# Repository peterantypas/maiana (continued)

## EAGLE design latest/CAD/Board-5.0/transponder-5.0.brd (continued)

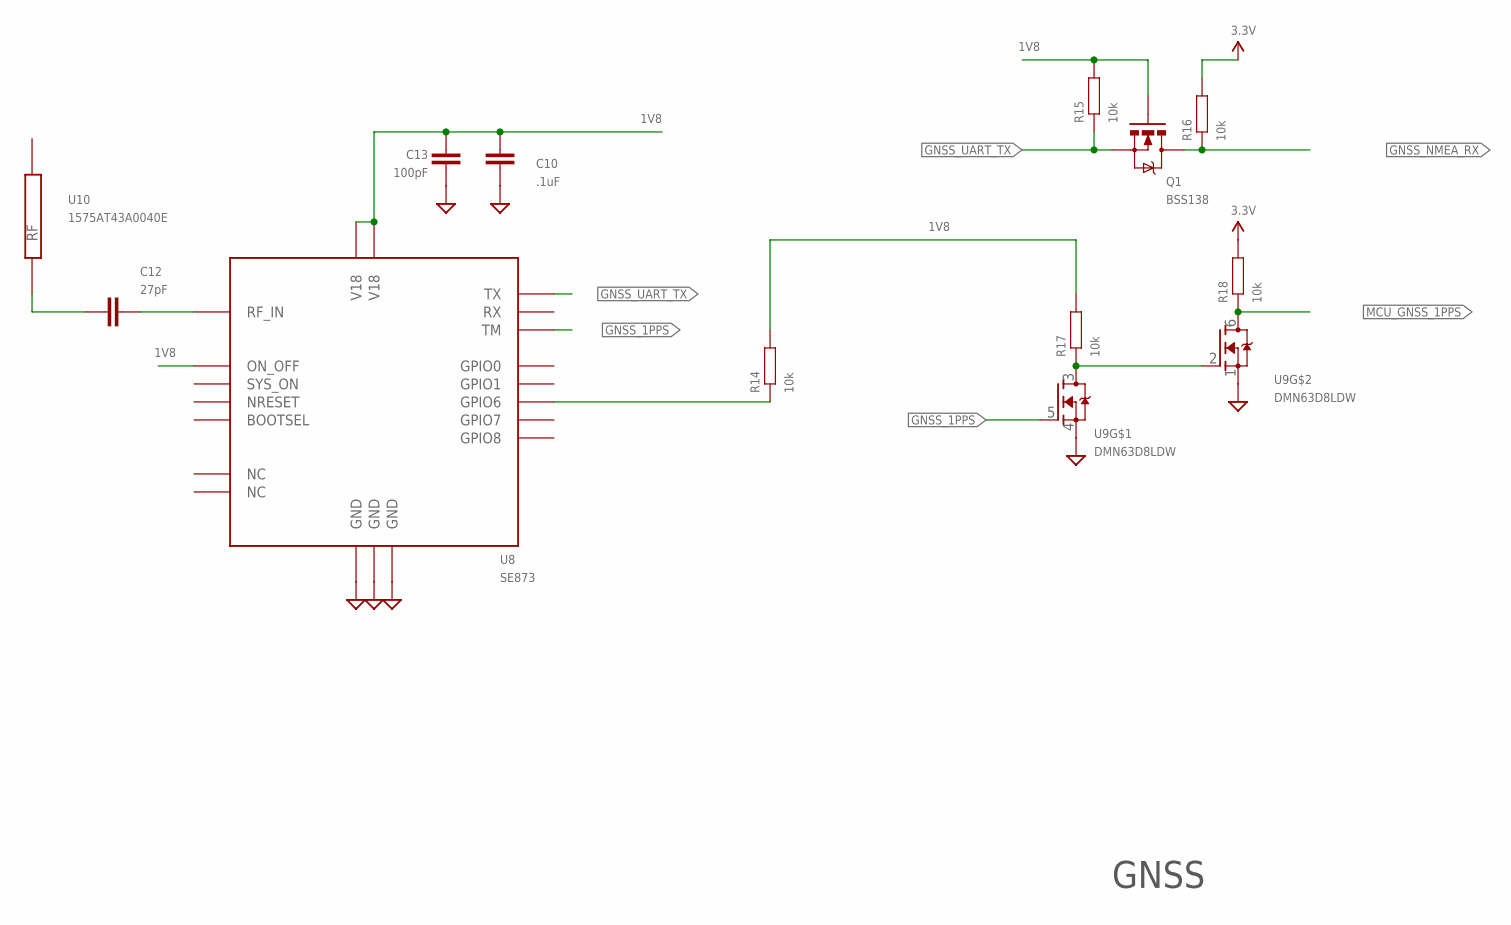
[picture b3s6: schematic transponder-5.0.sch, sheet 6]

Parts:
C10: .1uF; 0603-CAP
C12: 27pF; 0603-CAP
C13: 100pF; 0603-CAP
Q1: BSS138; SOT23-3
R14, R15, R16, R17, R18: 10k; 0603-RES
U8: SE873
U9: DMN63D8LDW; SOT363
U10: 1575AT43A0040E

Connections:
1V8: C10.1, C13.1, Q1.1 (G), R14.2, R15.2, R17.2, U8.P$3 (V18), U8.P$6 (ON_OFF), U8.P$19 (V18); also elsewhere on the board
3.3V: R16.2, R18.2; also elsewhere on the board
GND: C10.2, C13.2, U8.P$2 (GND), U8.P$10 (GND), U8.P$20 (GND), U9.1 (S), U9.4 (S); also elsewhere on the board
GNSS_1PPS: U8.P$11 (TM), U9.5 (G)
GNSS_NMEA_RX: Q1.3 (D), R16.1; also elsewhere on the board
GNSS_UART_TX: Q1.2 (S), R15.1, U8.P$15 (TX)
MCU_GNSS_1PPS: R18.1, U9.6 (D); also elsewhere on the board
unnamed: C12.2, U8.P$1 (RF_IN)
unnamed: C12.1, U10.P$1 (RF)
unnamed: R17.1, U9.2 (G), U9.3 (D)
unnamed: R14.1, U8.P$13 (GPIO6)

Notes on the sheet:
GNSS

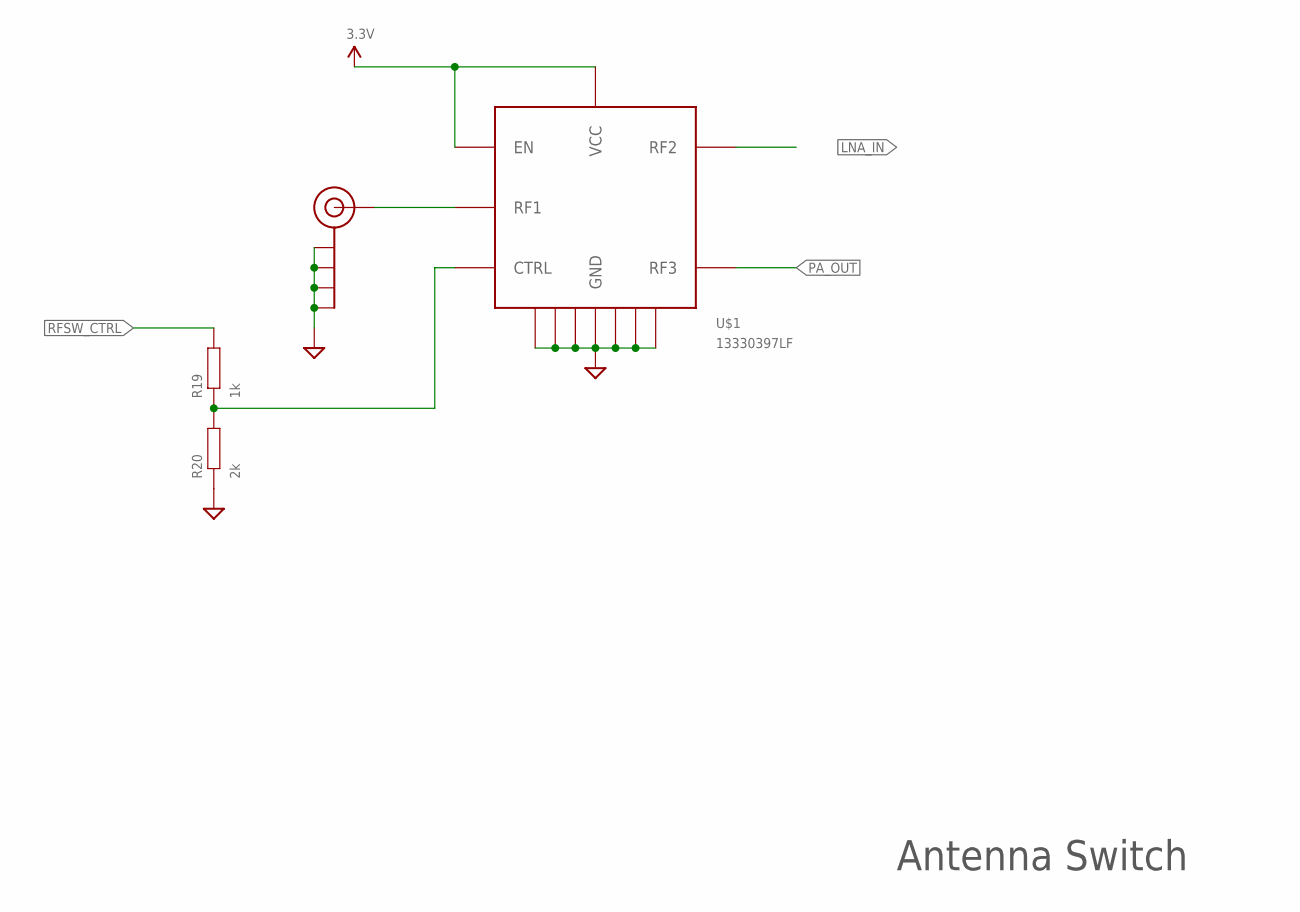
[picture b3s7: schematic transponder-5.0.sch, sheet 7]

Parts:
J$1: SMA_EDGE; SMA-EDGE
R19: 1k; 0603-RES
R20: 2k; 0603-RES
U$1: 13330397LF; QFN12

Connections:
3.3V: U$1.P$8 (EN), U$1.P$9 (VCC); also elsewhere on the board
GND: J$1.GND@0 (GND), J$1.GND@1 (GND), J$1.GND@2 (GND), J$1.GND@3 (GND), R20.1, U$1.P$1 (GND), U$1.P$3 (GND), U$1.P$4 (GND), U$1.P$6 (GND), U$1.P$10 (GND), U$1.P$12 (GND), U$1.P$13 (GND); also elsewhere on the board
LNA_IN: U$1.P$11 (RF2); also elsewhere on the board
unnamed: R19.1, R20.2, U$1.P$7 (CTRL)
unnamed: J$1.SIG (SIGNAL), U$1.P$2 (RF1)
PA_OUT: U$1.P$5 (RF3); also elsewhere on the board
RFSW_CTRL: R19.2; also elsewhere on the board

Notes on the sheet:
Antenna Switch

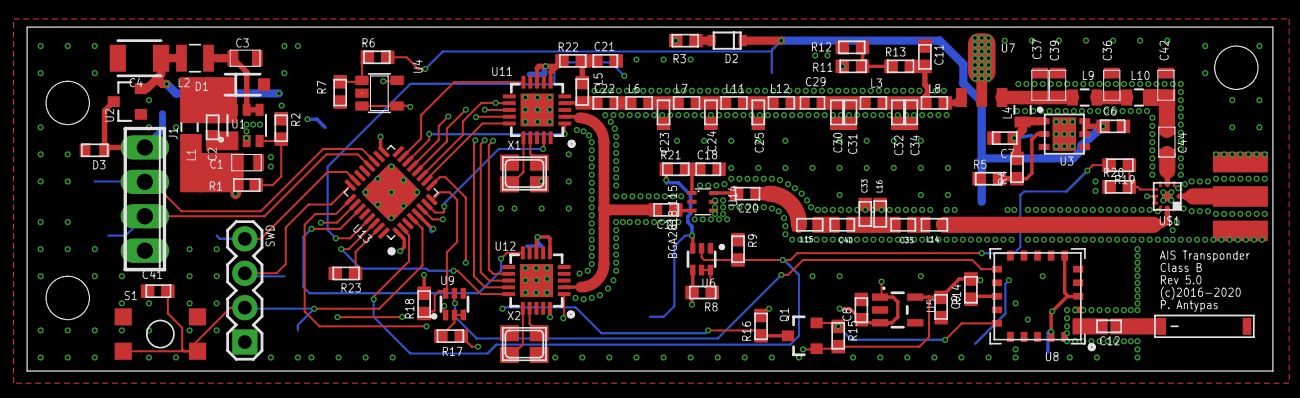
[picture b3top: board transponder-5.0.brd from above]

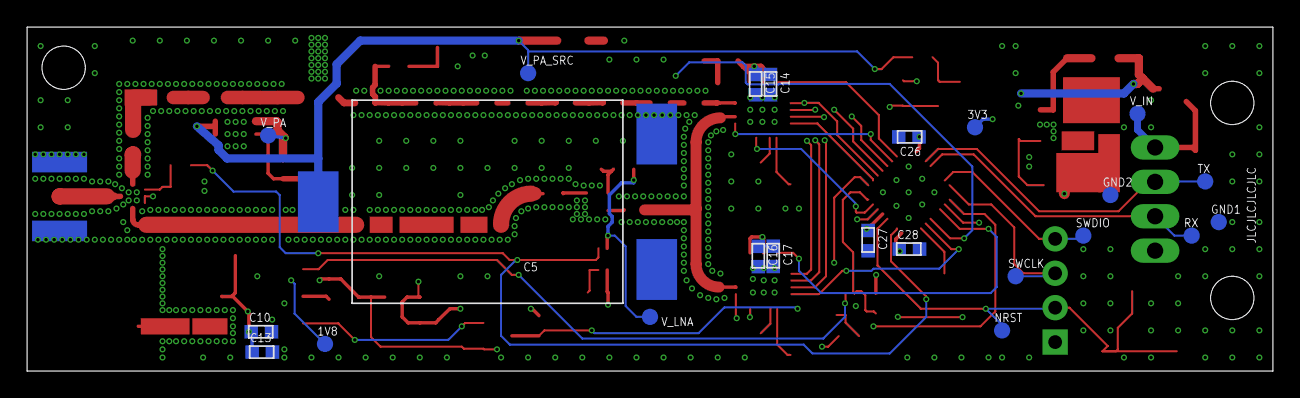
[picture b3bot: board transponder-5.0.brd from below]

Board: 4 copper layers, 92.0 x 25.4 mm, 117 parts (23 on the bottom side), 74 nets.

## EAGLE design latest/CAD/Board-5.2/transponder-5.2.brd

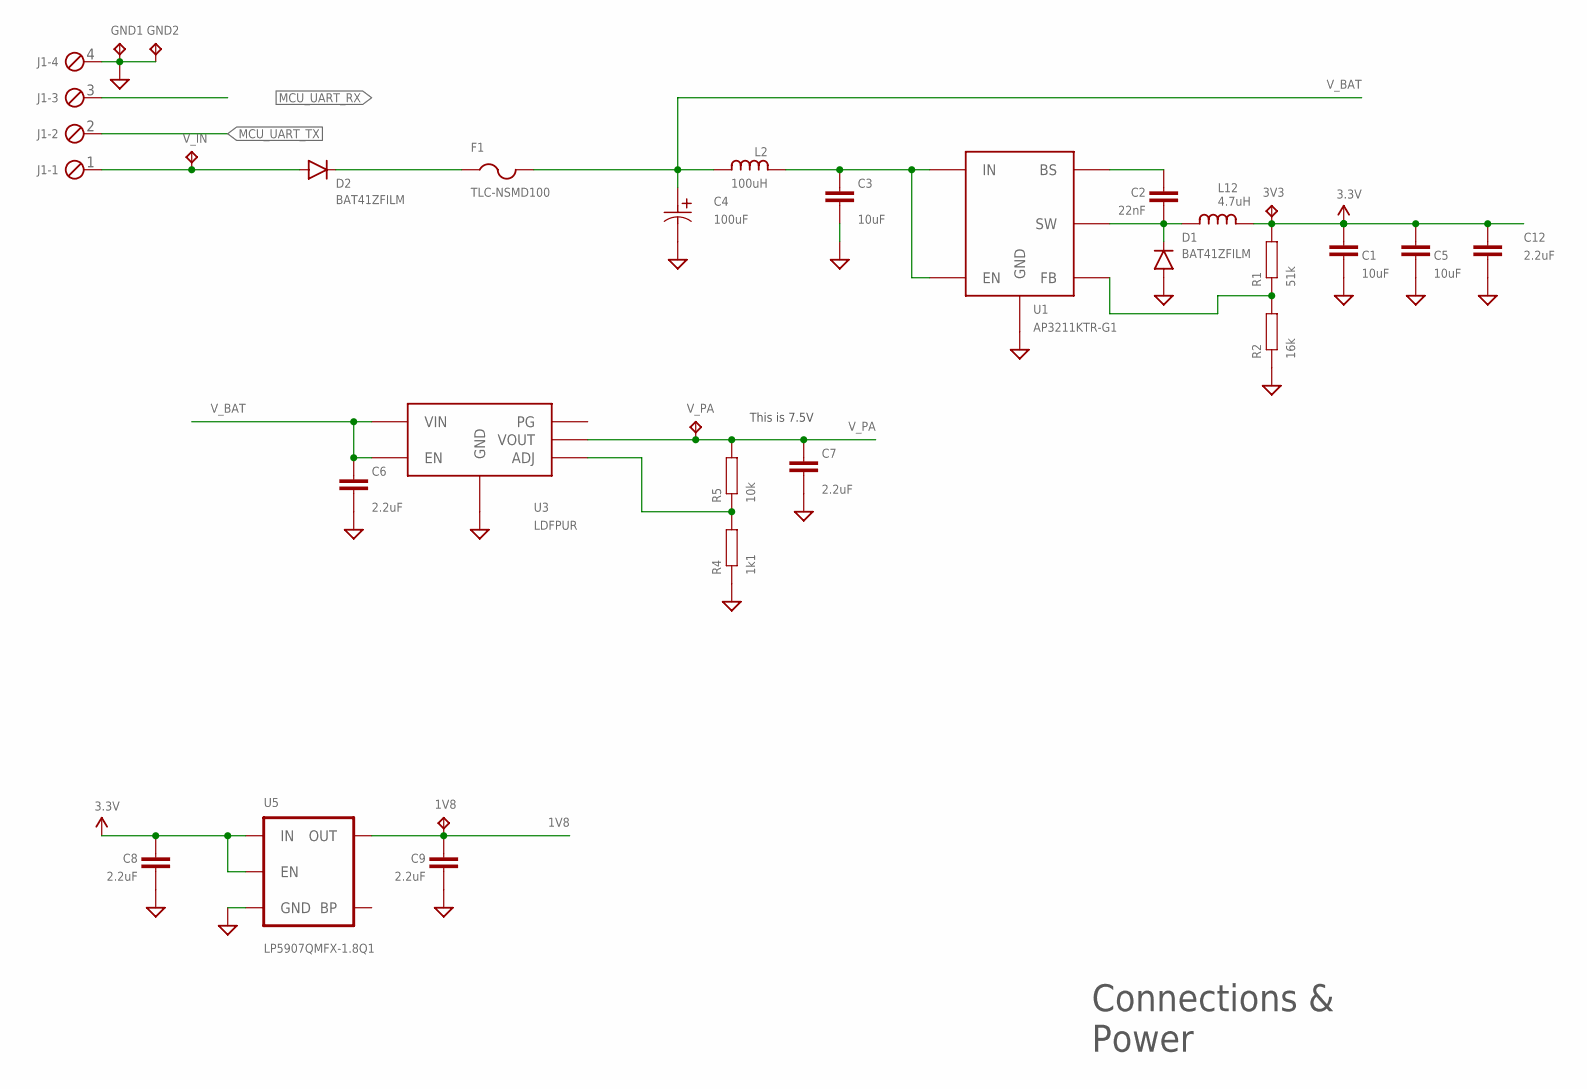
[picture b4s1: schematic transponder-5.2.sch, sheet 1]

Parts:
1V8, 3V3: TPTP16R; TP16R
C1, C3, C5: 10uF; 0805; PARTNO EMK212ABJ106KG-T
C2: 22nF; 0603-CAP; PARTNO GRM188R71E223KA01D
C4: 100uF; PCAP_6.3X5.4-ELECT; PARTNO UWX1C101MCL1GB
C6, C7, C8, C9, C12: 2.2uF; 0603-CAP; PARTNO EMK107BJ225KA-T
D1, D2: BAT41ZFILM; SOD-123; PARTNO BAT41ZFILM
F1: TLC-NSMD100; R1206; PARTNO TLC-NSMD100
GND1, GND2: TPTP16R; TP16R
J1: MPT4; 4POL254
L2: 100uH; 1206; PARTNO CBC3225T101KRV
L12: 4.7uH; 0805; PARTNO MLZ2012M4R7WT000
R1: 51k; 0603-RES; PARTNO RC0603JR-0751KL
R2: 16k; 0603-RES; PARTNO RC0603FR-1016KL
R4: 1k1; 0603-RES; PARTNO RC0603JR-071K1L
R5: 10k; 0603-RES; PARTNO RC0603JR-0710KL
U1: AP3211KTR-G1; SOT23-6; PARTNO AP3211KTR-G1
U3: LDFPUR; DFN-6; PARTNO LDFPUR
U5: LP5907QMFX-1.8Q1; SOT23-5; PARTNO LP5907QMFX-1.8Q1
V_IN: TPTP16R; TP16R
V_PA: TPTP16R; TP16R

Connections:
1V8: 1V8.TP, C9.1, U5.5 (OUT); also elsewhere on the board
3.3V: 3V3.TP, C1.1, C5.1, C8.1, C12.1, L12.P$2, R1.2, U5.1 (IN), U5.3 (EN); also elsewhere on the board
GND: C1.2, C3.2, C4.2 (22), C5.2, C6.2, C7.2, C8.2, C9.2, C12.2, D1.A, GND1.TP, GND2.TP, J1.4, R2.1, R4.1, U1.2 (GND), U3.P$4 (GND), U3.P$7 (GND), U5.2 (GND); also elsewhere on the board
MCU_UART_RX: J1.3; also elsewhere on the board
MCU_UART_TX: J1.2; also elsewhere on the board
unnamed: C3.1, L2.P$1, U1.4 (EN), U1.5 (IN)
unnamed: C2.2, D1.C, L12.P$1, U1.6 (SW)
unnamed: C2.1, U1.1 (BS)
unnamed: R1.1, R2.2, U1.3 (FB)
unnamed: R4.2, R5.1, U3.P$2 (ADJ)
unnamed: D2.C, F1.1
V_BAT: C4.1 (11), C6.1, F1.2, L2.P$2, U3.P$5 (EN), U3.P$6 (VIN)
V_IN: D2.A, J1.1, V_IN.TP
V_PA: C7.1, R5.2, U3.P$1 (VOUT), V_PA.TP; also elsewhere on the board

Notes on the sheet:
Connections & Power
This is 7.5V

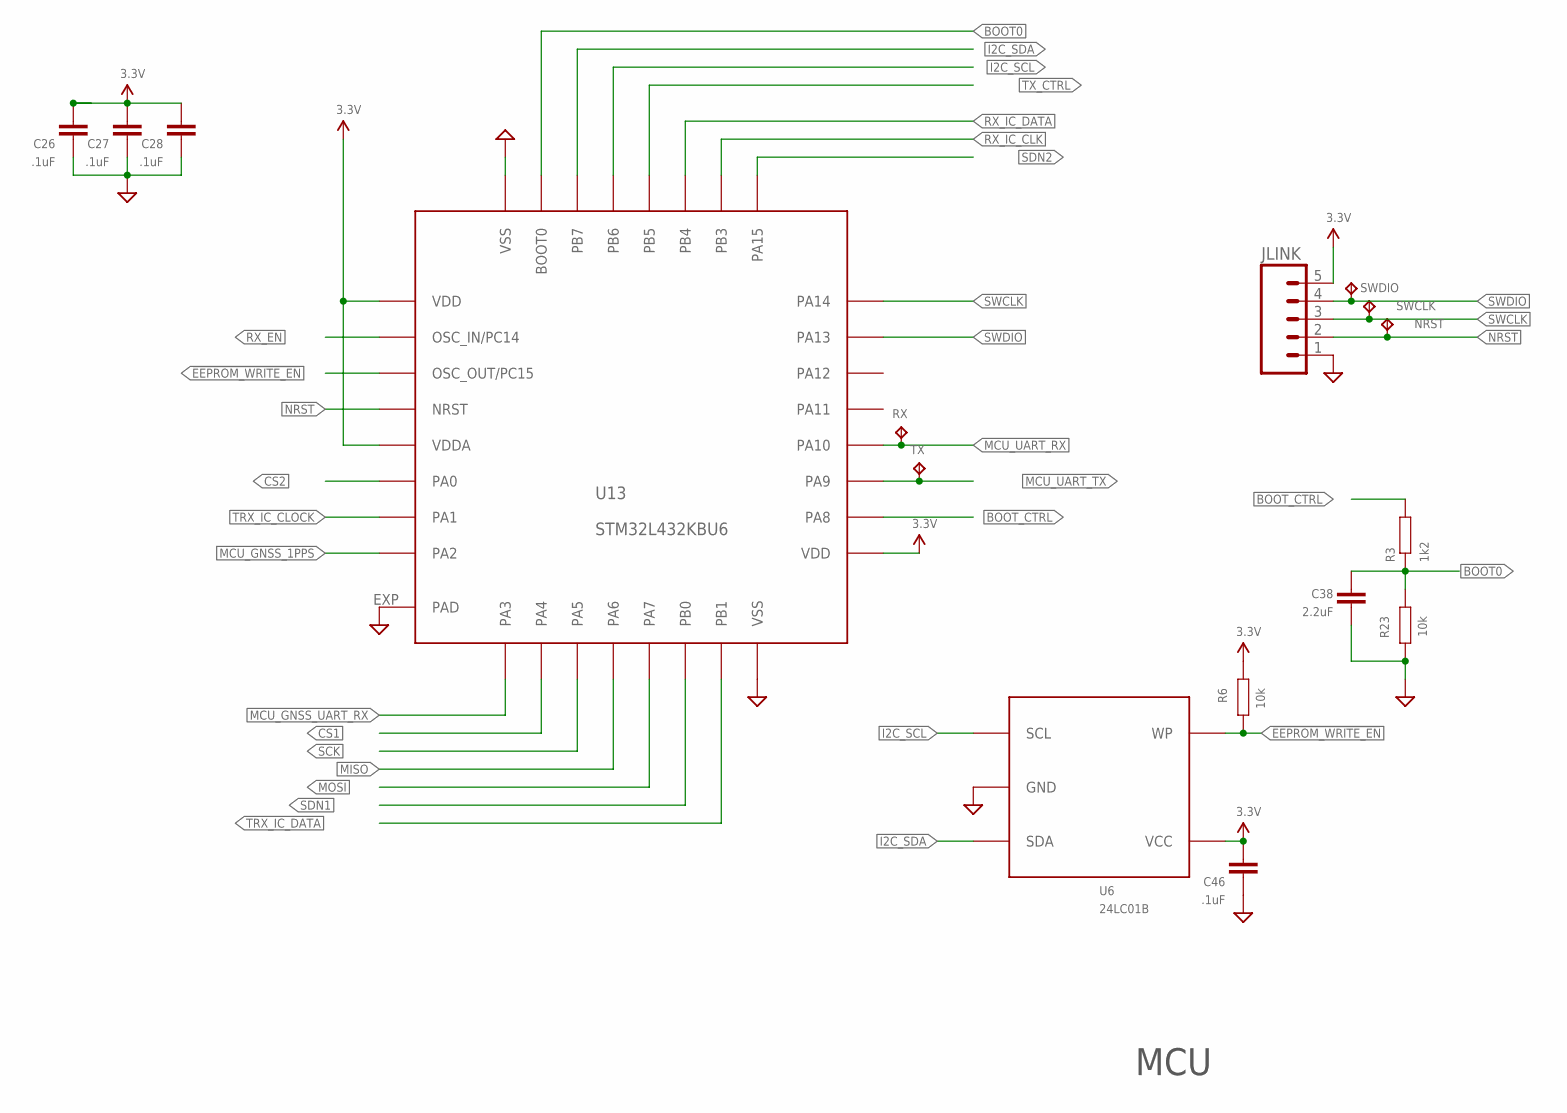
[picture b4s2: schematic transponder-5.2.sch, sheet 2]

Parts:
C26, C27, C28, C46: .1uF; 0603-CAP; PARTNO EMK107B7104KAHT
C38: 2.2uF; 0603-CAP; PARTNO EMK107BJ225KA-T
JLINK: M05PTH; 1X05
NRST: TPTP16R; TP16R
R3: 1k2; 0603-RES; PARTNO RC0603JR-071K2L
R6, R23: 10k; 0603-RES; PARTNO RC0603JR-0710KL
RX: TPTP16R; TP16R
SWCLK: TPTP16R; TP16R
SWDIO: TPTP16R; TP16R
TX: TPTP16R; TP16R
U6: 24LC01B; SOT23-5; PARTNO 24LC01BT-I/OT
U13: STM32L432KBU6; QFN32; PARTNO STM32L431KBU6

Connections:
3.3V: C26.1, C27.1, C28.1, C46.1, JLINK.5, R6.1, U6.4 (VCC), U13.1 (VDD), U13.5 (VDDA), U13.17 (VDD); also elsewhere on the board
!EEPROM_WRITE_EN: R6.2, U6.5 (WP), U13.3 (OSC_OUT/PC15)
BOOT0: C38.1, R3.1, R23.1, U13.31 (BOOT0)
BOOT_CTRL: R3.2, U13.18 (PA8)
CS1: U13.10 (PA4); also elsewhere on the board
CS2: U13.6 (PA0); also elsewhere on the board
GND: C26.2, C27.2, C28.2, C38.2, C46.2, JLINK.1, R23.2, U6.2 (GND), U13.16 (VSS), U13.32 (VSS), U13.EXP (PAD); also elsewhere on the board
I2C_SCL: U6.1 (SCL), U13.29 (PB6)
I2C_SDA: U6.3 (SDA), U13.30 (PB7)
MCU_GNSS_1PPS: U13.8 (PA2); also elsewhere on the board
MCU_GNSS_UART_RX: U13.9 (PA3); also elsewhere on the board
MCU_UART_RX: RX.TP, U13.20 (PA10); also elsewhere on the board
MCU_UART_TX: TX.TP, U13.19 (PA9); also elsewhere on the board
MISO: U13.12 (PA6); also elsewhere on the board
MOSI: U13.13 (PA7); also elsewhere on the board
NRST: JLINK.2, NRST.TP, U13.4 (NRST)
RX_EN: U13.2 (OSC_IN/PC14); also elsewhere on the board
RX_IC_CLK: U13.26 (PB3); also elsewhere on the board
RX_IC_DATA: U13.27 (PB4); also elsewhere on the board
SCK: U13.11 (PA5); also elsewhere on the board
SDN1: U13.14 (PB0); also elsewhere on the board
SDN2: U13.25 (PA15); also elsewhere on the board
SWCLK: JLINK.3, SWCLK.TP, U13.24 (PA14)
SWDIO: JLINK.4, SWDIO.TP, U13.23 (PA13)
TRX_IC_CLOCK: U13.7 (PA1); also elsewhere on the board
TRX_IC_DATA: U13.15 (PB1); also elsewhere on the board
TX_CTRL: U13.28 (PB5); also elsewhere on the board

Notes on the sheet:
MCU

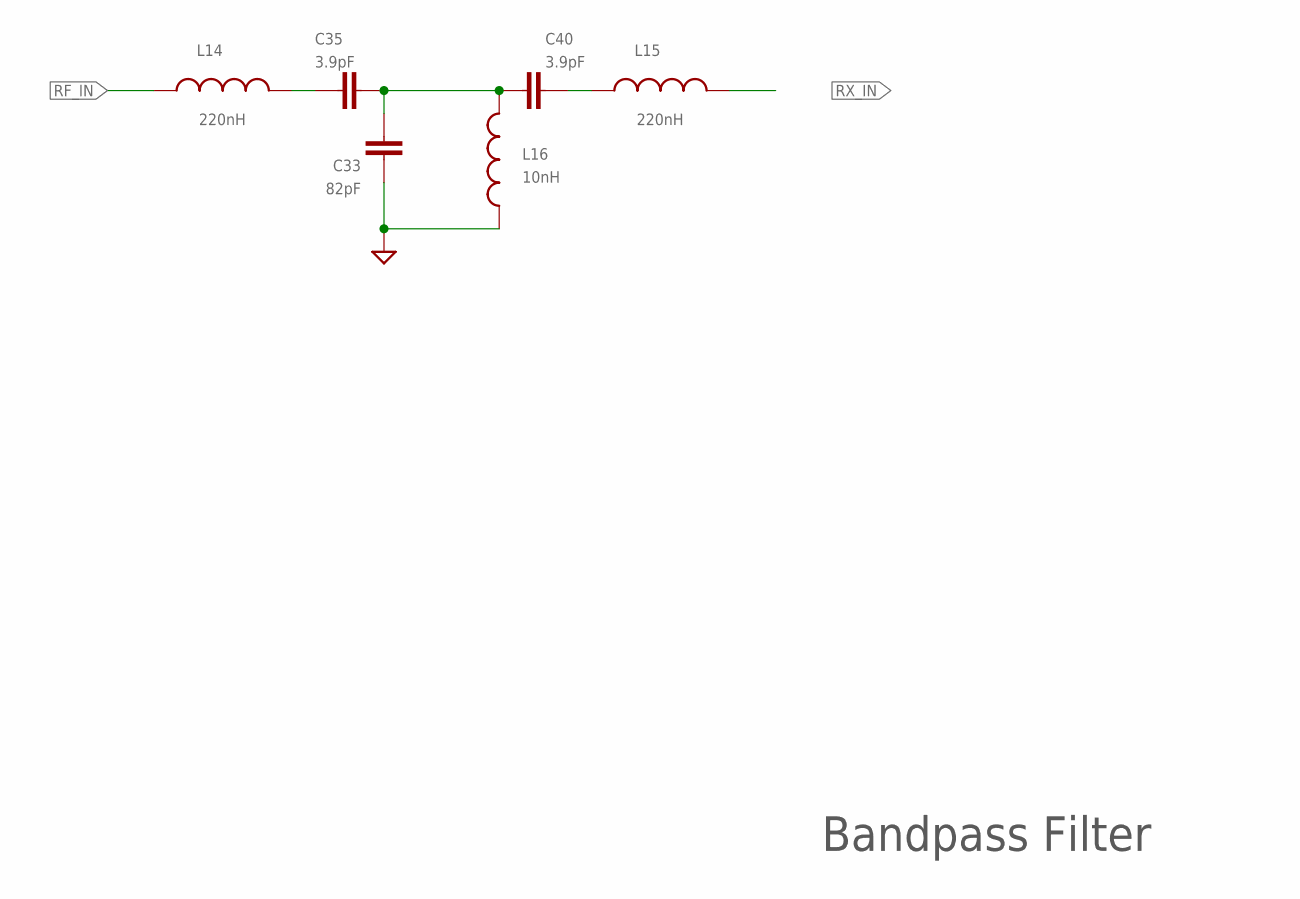
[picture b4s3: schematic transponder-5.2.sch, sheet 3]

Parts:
C33: 82pF; 0603-CAP
C35, C40: 3.9pF; 0603-CAP; PARTNO GCM1885C2A3R9BA16D
L14, L15: 220nH; 0603
L16: 10nH; 0603; PARTNO LQW18AS10NJ0CD

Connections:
GND: C33.1, L16.1; also elsewhere on the board
unnamed: C33.2, C35.1, C40.2, L16.2
unnamed: C40.1, L15.1
unnamed: C35.2, L14.2
RF_IN: L14.1; also elsewhere on the board
RX_IN: L15.2; also elsewhere on the board

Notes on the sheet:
Bandpass Filter

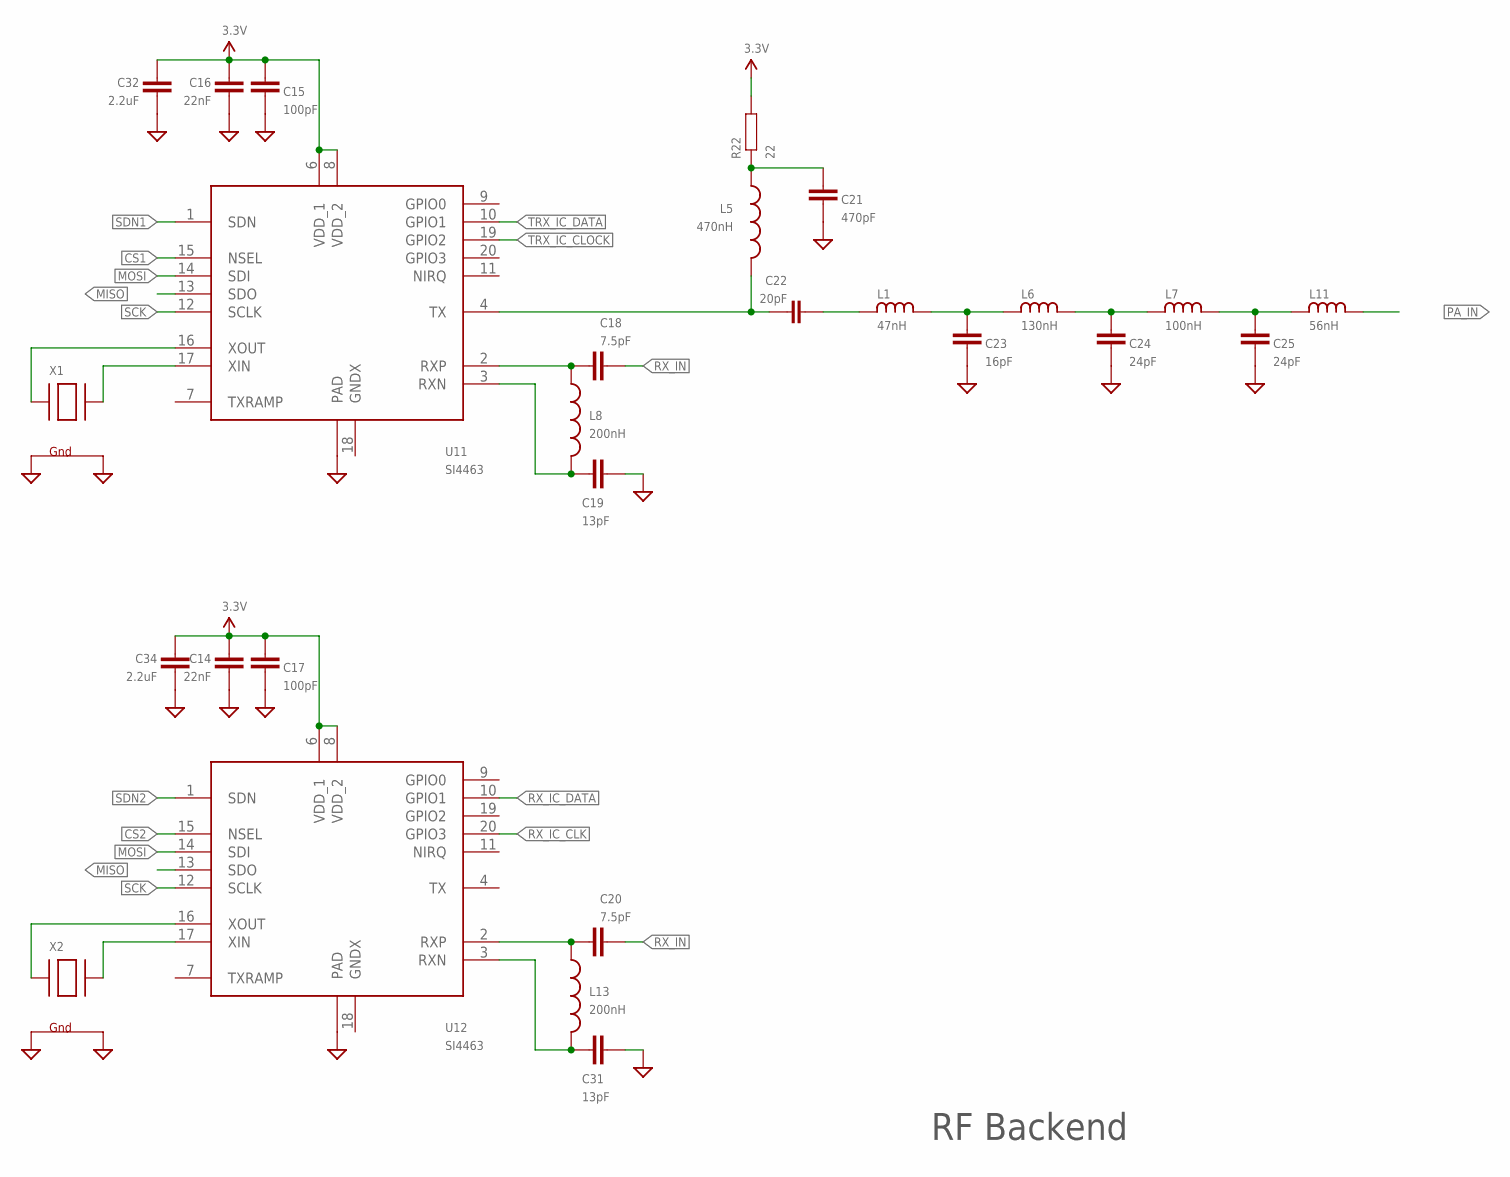
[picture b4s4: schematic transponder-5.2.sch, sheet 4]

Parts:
C14, C16: 22nF; 0603-CAP; PARTNO GRM188R71E223KA01D
C15, C17: 100pF; 0603-CAP; PARTNO GCM1885C2A101JA16D
C18, C20: 7.5pF; 0603-CAP; PARTNO GRM1885C1H7R5DA01D
C19, C31: 13pF; 0603-CAP; PARTNO GRM1885C1H130JA01D
C21: 470pF; 0603-CAP; PARTNO GCM1885C2A471JA16J
C22: 20pF; 0603; PARTNO GRM1885C1H200JA01D
C23: 16pF; 0603-CAP; PARTNO GCM1885C2A160JA16D
C24, C25: 24pF; 0603-CAP; PARTNO GCM1885C2A240JA16D
C32, C34: 2.2uF; 0603-CAP; PARTNO EMK107BJ225KA-T
L1: 47nH; 0603; PARTNO LQW18AS47NG00D
L5: 470nH; 0603; PARTNO HK1608R47J-T
L6: 130nH; 0603; PARTNO LQW18ANR13G00D
L7: 100nH; 0603; PARTNO LQW18ANR10G00D
L8, L13: 200nH; 0603; PARTNO LQW18ANR20J00D
L11: 56nH; 0603; PARTNO LQW18AN56NG00D
R22: 22; 0603-RES; PARTNO RC0603JR-0722RL
U11, U12: SI4463; PARTNO SI4463-C2A-GMR
X1, X2: XTAL-4-3225; NX3225; PARTNO CX3225SB30000D0FPLCC

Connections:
3.3V: C14.1, C15.1, C16.1, C17.1, C32.1, C34.1, R22.2, U11.6 (VDD_1), U11.8 (VDD_2), U12.6 (VDD_1), U12.8 (VDD_2); also elsewhere on the board
CS1: U11.15 (NSEL); also elsewhere on the board
CS2: U12.15 (NSEL); also elsewhere on the board
GND: C14.2, C15.2, C16.2, C17.2, C19.1, C21.2, C23.2, C24.2, C25.2, C31.1, C32.2, C34.2, U11.EXP (PAD), U12.EXP (PAD), X1.2 (G2), X1.4 (G1), X2.2 (G2), X2.4 (G1); also elsewhere on the board
MISO: U11.13 (SDO), U12.13 (SDO); also elsewhere on the board
MOSI: U11.14 (SDI), U12.14 (SDI); also elsewhere on the board
unnamed: C19.2, L8.2, U11.3 (RXN)
unnamed: C18.1, L8.1, U11.2 (RXP)
unnamed: C24.1, L6.P$2, L7.P$1
unnamed: C25.1, L7.P$2, L11.P$1
unnamed: C23.1, L1.P$2, L6.P$1
unnamed: U12.16 (XOUT), X2.1 (X1)
unnamed: U12.17 (XIN), X2.3 (X2)
unnamed: U11.16 (XOUT), X1.1 (X1)
unnamed: U11.17 (XIN), X1.3 (X2)
unnamed: C20.1, L13.1, U12.2 (RXP)
unnamed: C31.2, L13.2, U12.3 (RXN)
unnamed: C22.P$1, L5.2, U11.4 (TX)
unnamed: C21.1, L5.1, R22.1
unnamed: C22.P$2, L1.P$1
PA_IN: L11.P$2; also elsewhere on the board
RX_IC_CLK: U12.20 (GPIO3); also elsewhere on the board
RX_IC_DATA: U12.10 (GPIO1); also elsewhere on the board
RX_IN: C18.2, C20.2; also elsewhere on the board
SCK: U11.12 (SCLK), U12.12 (SCLK); also elsewhere on the board
SDN1: U11.1 (SDN); also elsewhere on the board
SDN2: U12.1 (SDN); also elsewhere on the board
TRX_IC_CLOCK: U11.19 (GPIO2); also elsewhere on the board
TRX_IC_DATA: U11.10 (GPIO1); also elsewhere on the board

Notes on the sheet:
RF Backend

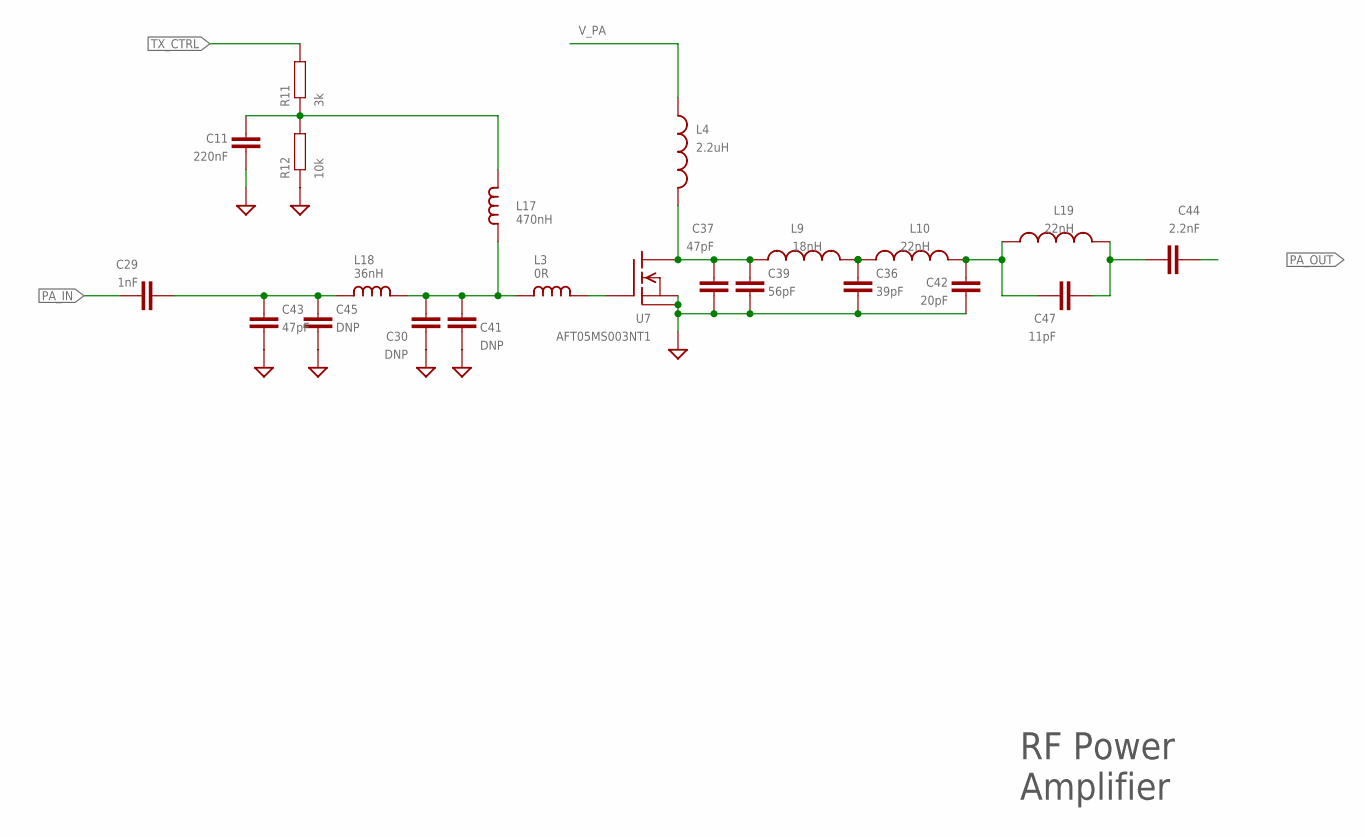
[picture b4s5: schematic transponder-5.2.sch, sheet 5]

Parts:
C11: 220nF; 0603-CAP
C29: 1nF; 0603-CAP; PARTNO GRM1885C1H102JA01D
C30: DNP; 0603-CAP; PARTNO GCM1885C2A101JA16D
C36: 39pF; 0603-CAP; PARTNO GRM1885C1H390JA01D
C37, C43: 47pF; 0603-CAP
C39: 56pF; 0603-CAP; PARTNO GRM1885C1H560JA01D
C41: DNP; 0603-CAP; PARTNO Murata Electronics
C42: 20pF; 0603-CAP; PARTNO GRM1885C1H200JA01D
C44: 2.2nF; 0603-CAP; PARTNO GRM1885C1H222JA01J
C45: DNP; 0603-CAP; PARTNO GRM1885C1H560JA01D
C47: 11pF; 0603-CAP; PARTNO GRM1885C1H110JA01D
L3: 0R; 0603; PARTNO LQW18AN11NJ00D
L4: 2.2uH; 0805; PARTNO BRC2012T2R2MD
L9: 18nH; 0603; PARTNO LQW18AN18NG00D
L10, L19: 22nH; 0603; PARTNO LQW18AN22NJ00D
L17: 470nH; 0603; PARTNO HK1608R47J-T
L18: 36nH; 0603
R11: 3k; 0603-RES
R12: 10k; 0603-RES; PARTNO RC0603JR-0710KL
U7: AFT05MS003NT1; SOT-89; PARTNO AFT05MS003NT1

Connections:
GND: C11.2, C30.2, C36.2, C37.2, C39.2, C41.2, C42.2, C43.2, C45.2, R12.1, U7.2 (S), U7.2@1 (PAD); also elsewhere on the board
unnamed: C11.1, L17.P$2, R11.1, R12.2
unnamed: C37.1, C39.1, L4.2, L9.1, U7.3 (D)
unnamed: L3.P$2, U7.1 (G)
unnamed: C36.1, L9.2, L10.1
unnamed: C29.2, C43.1, C45.1, L18.P$1
unnamed: C30.1, C41.1, L3.P$1, L17.P$1, L18.P$2
unnamed: C44.1, C47.2, L19.2
unnamed: C42.1, C47.1, L10.2, L19.1
PA_IN: C29.1; also elsewhere on the board
PA_OUT: C44.2; also elsewhere on the board
TX_CTRL: R11.2; also elsewhere on the board
V_PA: L4.1; also elsewhere on the board

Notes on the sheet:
RF Power Amplifier

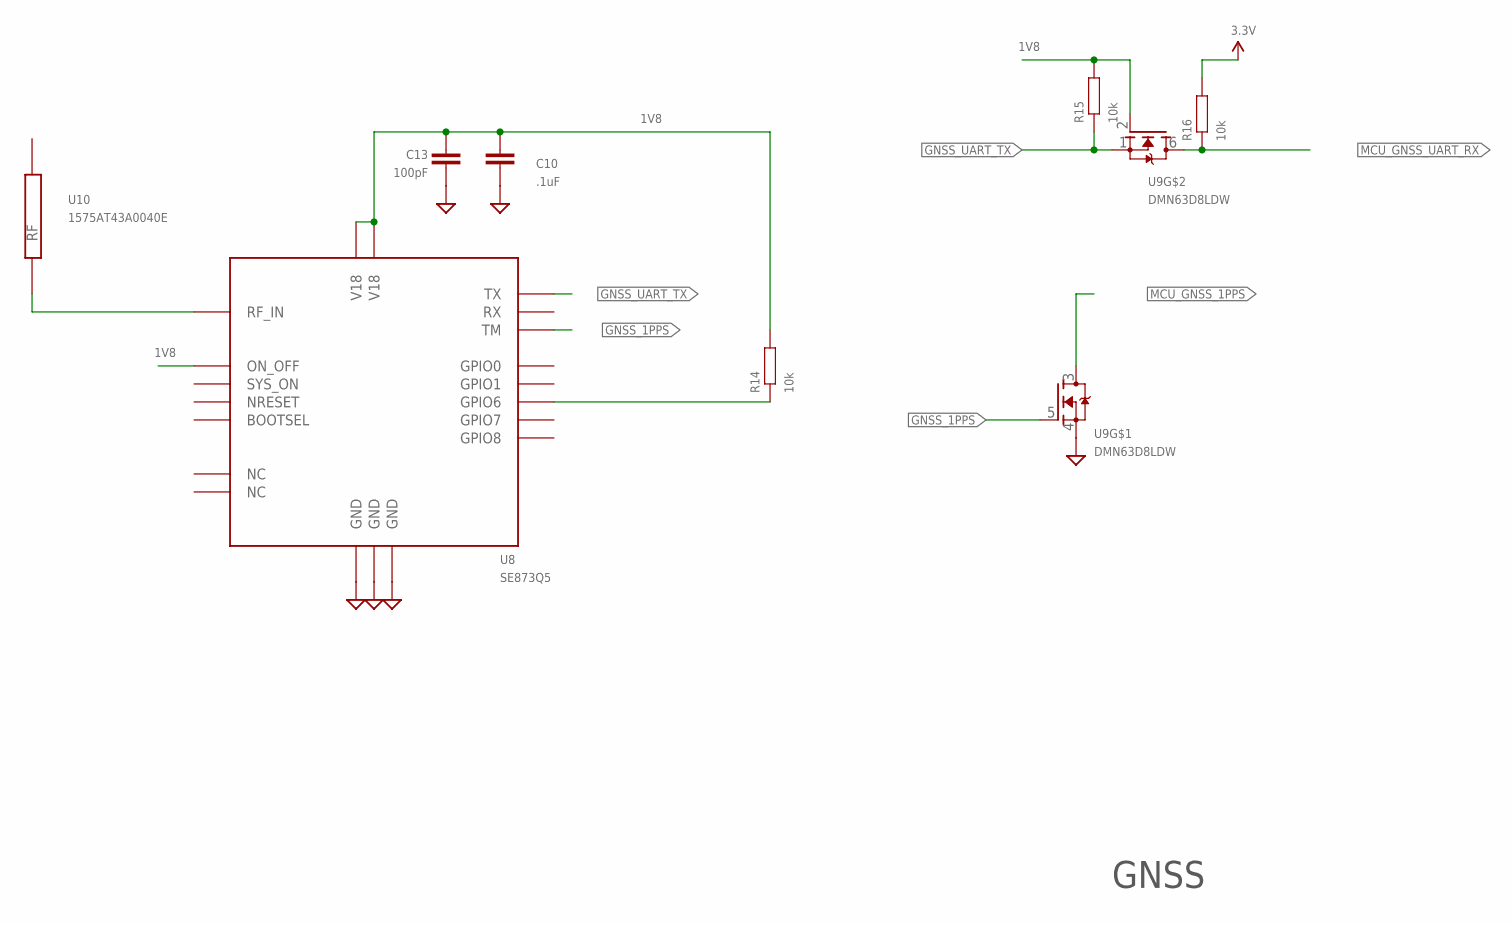
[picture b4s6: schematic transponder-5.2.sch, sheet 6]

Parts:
C10: .1uF; 0603-CAP; PARTNO EMK107B7104KAHT
C13: 100pF; 0603-CAP; PARTNO GCM1885C2A101JA16D
R14, R15, R16: 10k; 0603-RES; PARTNO RC0603JR-0710KL
U8: SE873Q5; SE873; PARTNO SE873Q5
U9: DMN63D8LDW; SOT363; PARTNO DMN63D8LDW
U10: 1575AT43A0040E; PARTNO 1575AT43A0040E

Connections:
1V8: C10.1, C13.1, R14.2, R15.2, U8.P$3 (V18), U8.P$6 (ON_OFF), U8.P$19 (V18), U9.2 (G); also elsewhere on the board
3.3V: R16.2; also elsewhere on the board
GND: C10.2, C13.2, U8.P$2 (GND), U8.P$10 (GND), U8.P$20 (GND), U9.4 (S); also elsewhere on the board
GNSS_1PPS: U8.P$11 (TM), U9.5 (G)
GNSS_UART_TX: R15.1, U8.P$15 (TX), U9.1 (S)
MCU_GNSS_1PPS: U9.3 (D); also elsewhere on the board
MCU_GNSS_UART_RX: R16.1, U9.6 (D); also elsewhere on the board
unnamed: U8.P$1 (RF_IN), U10.P$1 (RF)
unnamed: R14.1, U8.P$13 (GPIO6)

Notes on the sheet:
GNSS

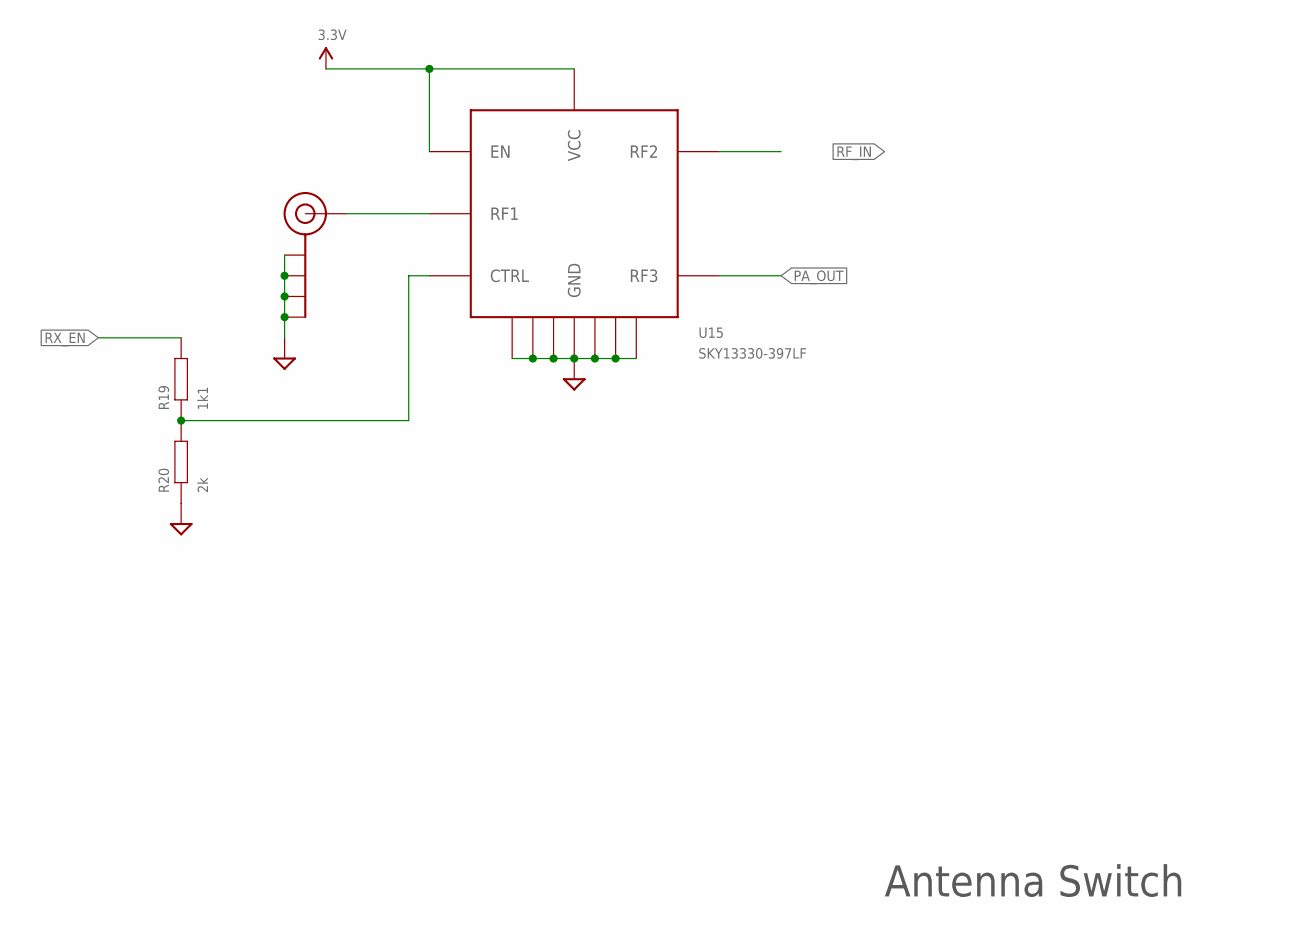
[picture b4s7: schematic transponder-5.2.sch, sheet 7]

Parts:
J$1: SMA_EDGE; SMA-EDGE
R19: 1k1; 0603-RES
R20: 2k; 0603-RES; PARTNO RC0603FR-072KL
U15: SKY13330-397LF; QFN12; PARTNO SKY13330-397LF

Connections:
3.3V: U15.P$8 (EN), U15.P$9 (VCC); also elsewhere on the board
GND: J$1.GND@0 (GND), J$1.GND@1 (GND), J$1.GND@2 (GND), J$1.GND@3 (GND), R20.1, U15.P$1 (GND), U15.P$3 (GND), U15.P$4 (GND), U15.P$6 (GND), U15.P$10 (GND), U15.P$12 (GND), U15.P$13 (GND); also elsewhere on the board
unnamed: R19.1, R20.2, U15.P$7 (CTRL)
unnamed: J$1.SIG (SIGNAL), U15.P$2 (RF1)
PA_OUT: U15.P$5 (RF3); also elsewhere on the board
RF_IN: U15.P$11 (RF2); also elsewhere on the board
RX_EN: R19.2; also elsewhere on the board

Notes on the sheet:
Antenna Switch

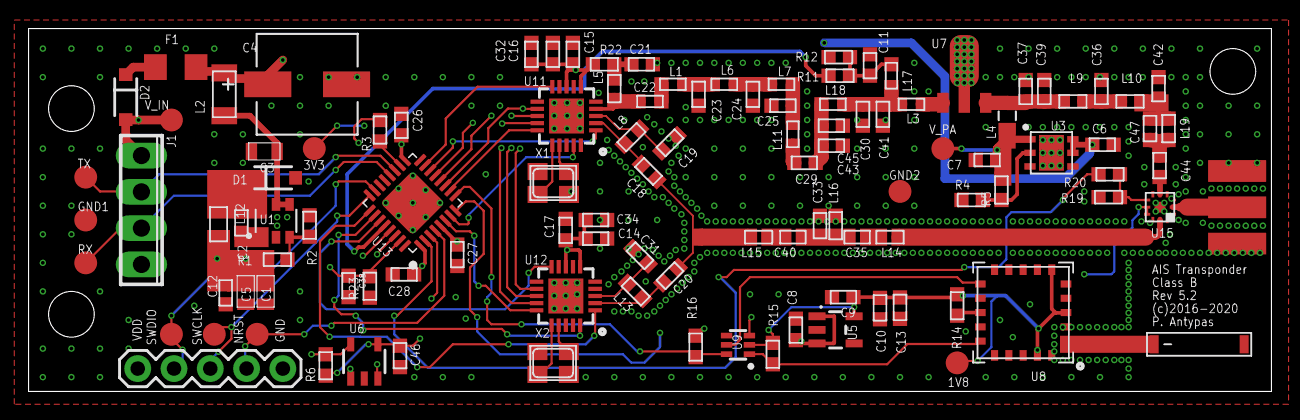
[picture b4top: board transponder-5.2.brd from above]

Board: 4 copper layers, 87.0 x 25.4 mm, 112 parts (0 on the bottom side), 72 nets.

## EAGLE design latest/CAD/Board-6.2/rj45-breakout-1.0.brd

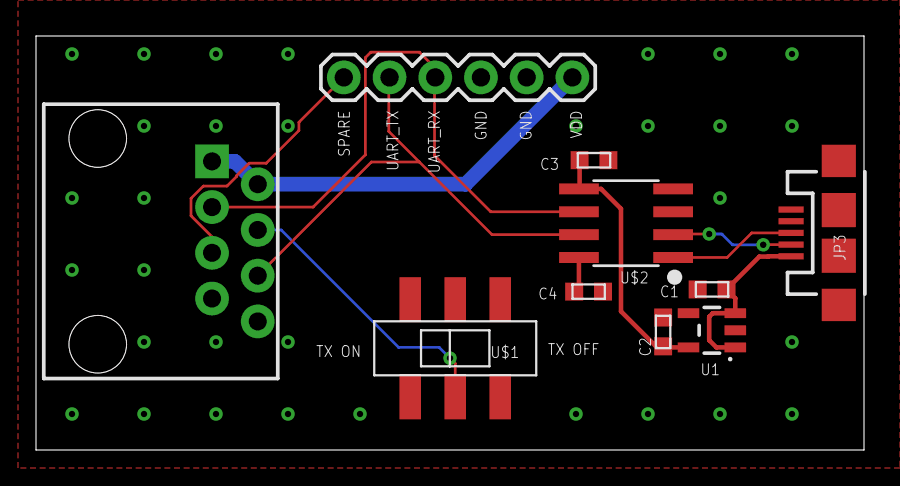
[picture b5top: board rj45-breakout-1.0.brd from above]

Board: 2 copper layers, 46.0 x 23.0 mm, 10 parts (0 on the bottom side), 11 nets.

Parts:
C1, C2: 1uF; 0603
C3, C4: 0.1uF; 0603
JP1: RJ45; RJ45-8
JP2: 1X06
JP3: USB-MICROB
U1: MCP1802T-3302I/OT; SOT23-5
U$1: JS202011SCQN; DPDT-SMD
U$2: CH330N; SOIC-8

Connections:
3.3V: C2.P$1, C3.P$1, U1.5, U$2.5
GND: C1.P$2, C2.P$2, C3.P$2, C4.P$2, JP1.7, JP1.8, JP2.4, JP2.5, JP3.GND, JP3.MT1, JP3.MT2, U1.2, U$1.P$6, U$2.3
unnamed: C4.P$1, U$2.8
SPARE: JP1.5, JP2.1
TRANSPONDER_RX: JP1.3, JP2.3, U$2.6
TRANSPONDER_TX: JP1.6, JP2.2, U$2.7
TX_OFF: JP1.4, U$1.P$5
USB_DM: JP3.D-, U$2.2
USB_DP: JP3.D+, U$2.1
VDD: JP1.1, JP1.2, JP2.6
V_BUS: C1.P$1, JP3.VBUS, U1.1, U1.3
